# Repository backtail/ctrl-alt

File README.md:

# CTRL+ALT

CTRL+ALT is a modular firmware and hardware platform for a STM8 microcontroller, focused on real-time audio, control voltage (CV), and lo-fi digital signal processing. It is designed for experimentation, eurorack synths and embedded control projects.

Currently, the framework comes with these example projects to help you get started and familiarise yourself on how to access the functionalities:
- blinky
- master clock
- sample & hold
- wavetable LFO

If you fork this repo and come up with your own cool program, feel free to contribute so that everyone can enjoy it!

## Getting Started

### Prerequisites

- [PlatformIO](https://platformio.org/) (for building and uploading firmware)
- [ctrl+alt](https://www.maxgenson.de/ctrl-alt/) eurorack module
- STM8 debug probe
- [VSCode](https://code.visualstudio.com/) (optional, but really good integration and generally recommended for this project)
- [VSCodium](https://vscodium.com/) (optional, PlatformIO not natively supported, however workaround [exists](https://www.kentoseth.com/posts/2023/mar/22/install-platformio-ide-in-vscodium-flatpak/))

### Getting Started

Install VSCode with PlatformIO Plugin (recommended) or the PlatformIO CLI tool.

```sh
$ git clone https://github.com/backtail/ctrl-alt
$ cd ctrl-alt
$ code . # open VSCode
```

All example projects are located in `src/programs/`.

### Building

Use the VSCode/Codium PIO task and set the right project/environment. (recommended)

or

```sh
$ pio run -e <project_name>
```

### Upload

Use the VSCode/Codium PIO task and set the right project/environment. (recommended)

or

```sh
$ pio run -e <project_name> -t upload
```

## The Complementary Hardware

This framework is made to run on the 6 HP wide CTRL+ALT eurorack module which can be found under `hardware/`.

It features:
- 3 logic inputs (threshold ~ 2.5V, 12V tolerable) + indicator LEDs
- 3 CV inputs (0V to 5V, 12V tolerable)
- 3 knobs
- up to 3 CV outputs (0V to 5V) or up to 3 logic outputs (0V or 5V) + indicator LEDs -> per output switchable via software
- 1 toggle switch
- 1 momentary button switch

## Contributing

Please read [CONTRIBUTING.md]() for details on our code of conduct, and the process for submitting pull requests to us.

### Authors

* **[Max Genson](https://www.maxgenson.de/)** - Engineer @ [KOMA Elektronik](https://koma-elektronik.com/new/about-shop/)

## License
The underlying hardware project source code is licensed under [CERN Open Hardware Licence Version 2 - Strongly Reciprocal](LICENSE_HARDWARE). 

Everything else, including the source code of the firmware for the CTRL+ALT hardware is licensed under [GPL-3.0](LICENSE_SOFTWARE).

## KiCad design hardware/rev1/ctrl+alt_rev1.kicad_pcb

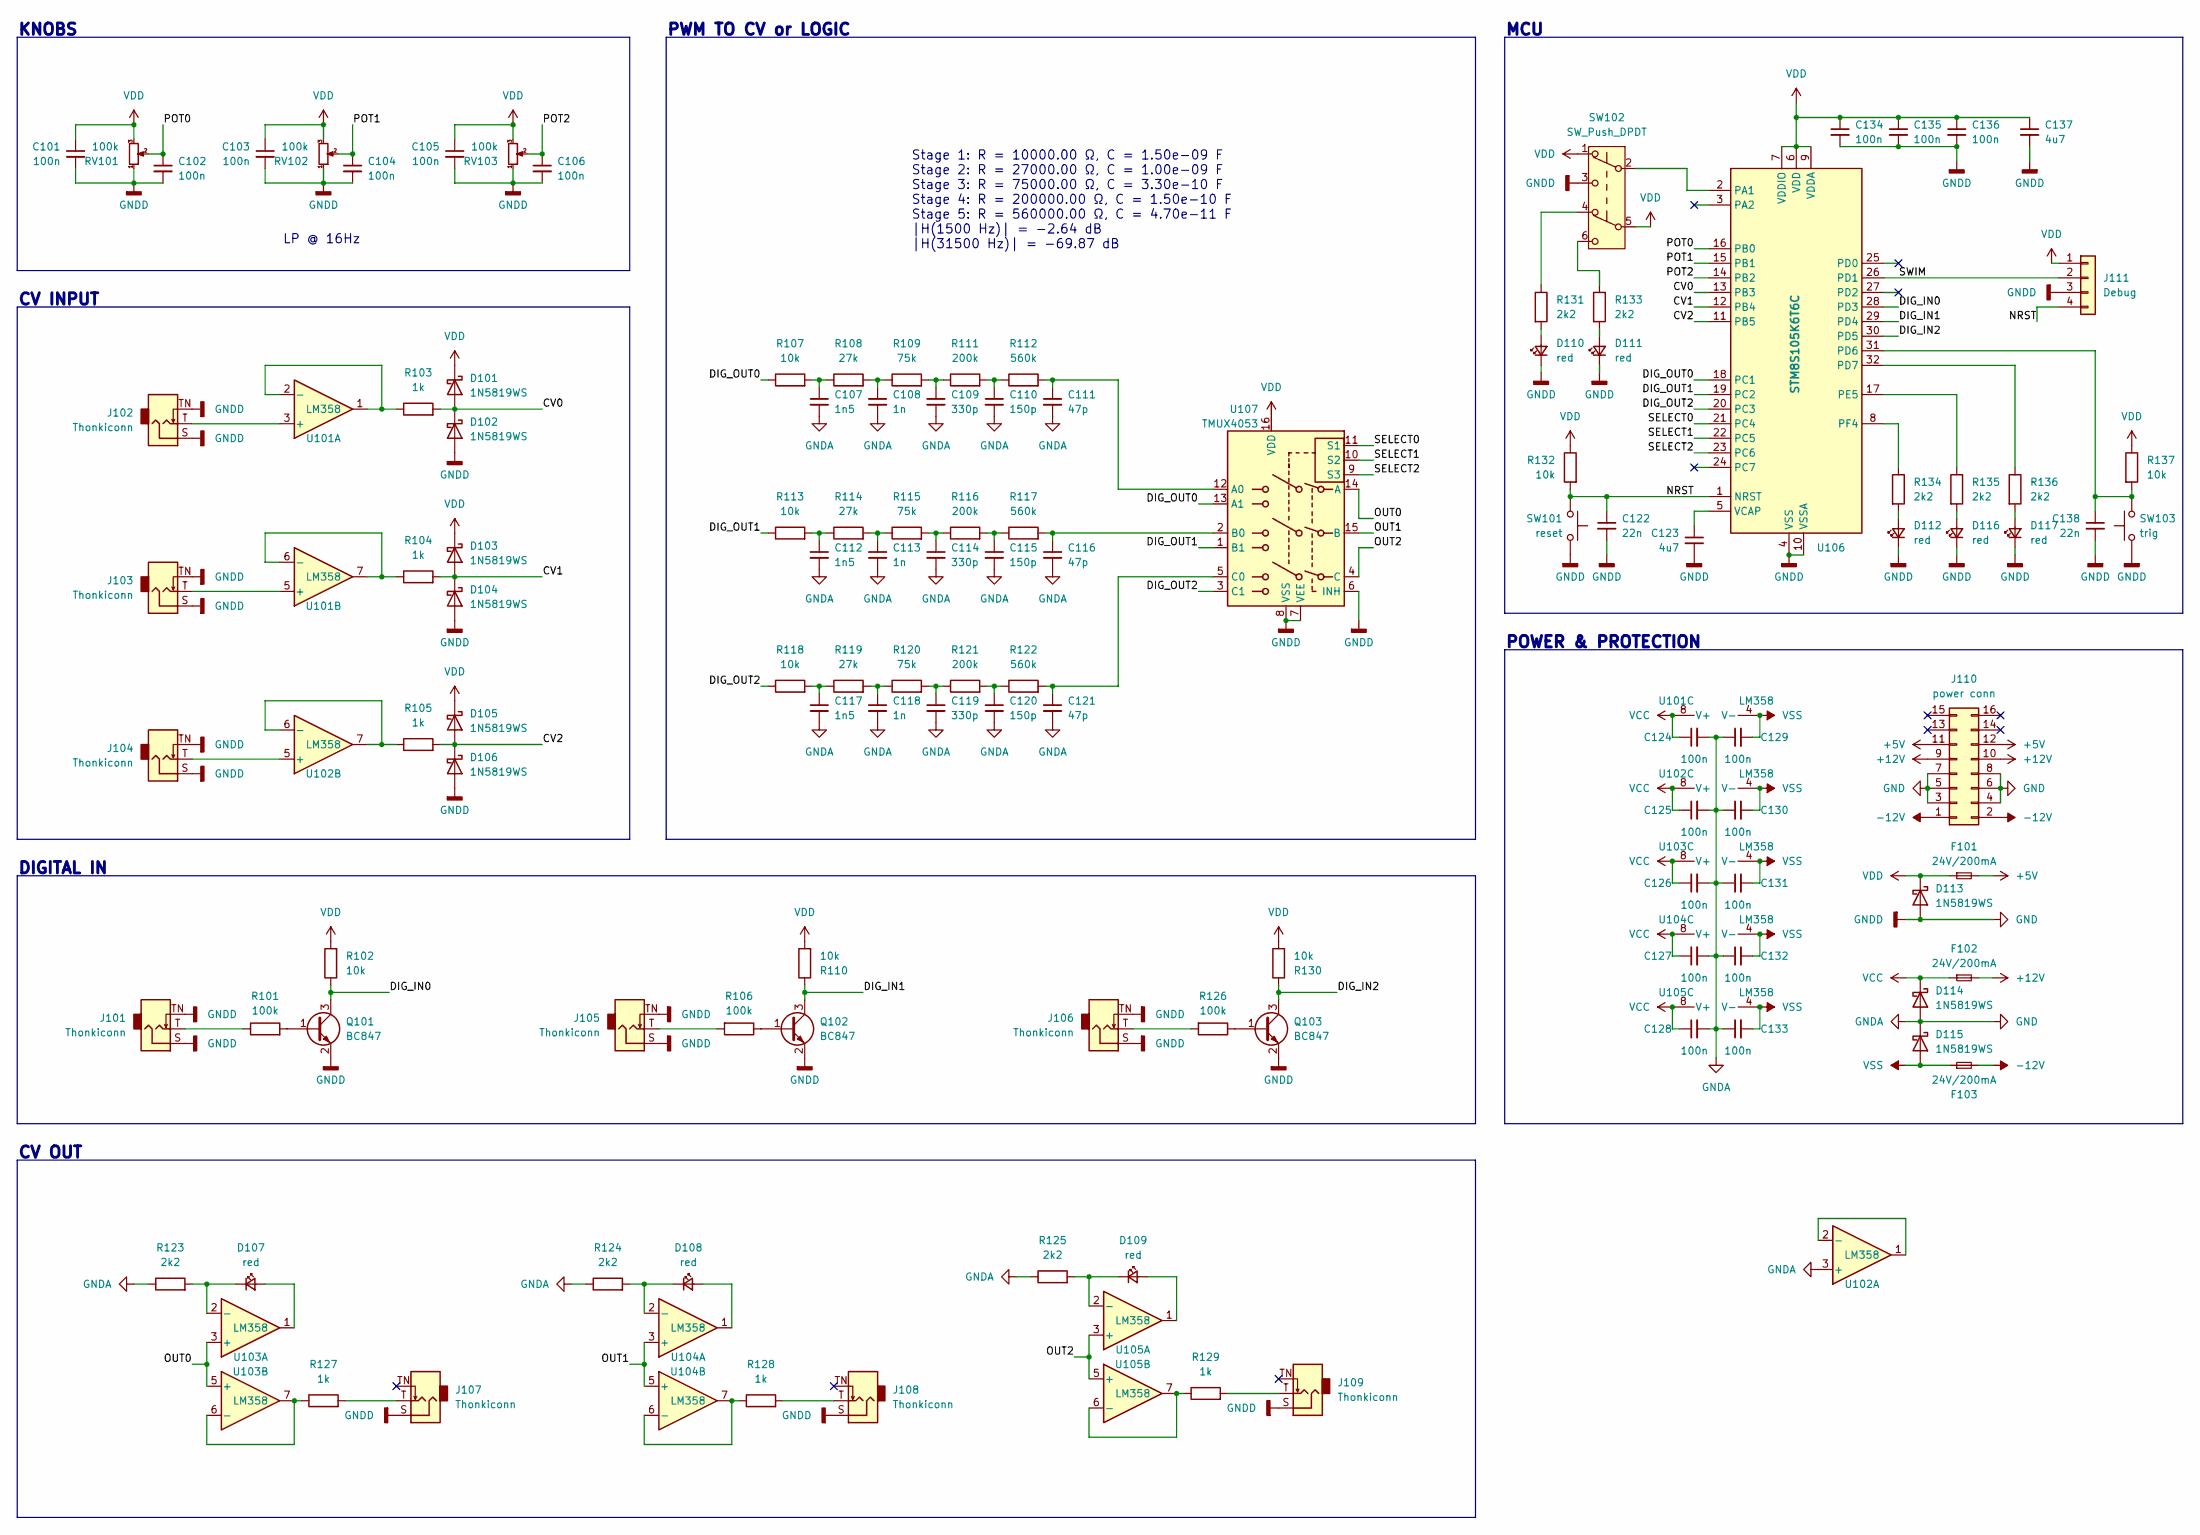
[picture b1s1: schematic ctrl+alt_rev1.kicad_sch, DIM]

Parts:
C101, C102, C103, C104, C105, C106, C124, C125, C126, C127, C128, C129, C130, C131, C132, C133, C134, C135, C136: 100n; C_0402_1005Metric; LCSC Part # C1523
C107, C112, C117: 1n5; C_0603_1608Metric; LCSC Part # C1595
C108, C113, C118: 1n; C_0402_1005Metric; LCSC Part # C1523
C109, C114, C119: 330p; C_0402_1005Metric; LCSC Part # C13533
C110, C115, C120: 150p; C_0402_1005Metric; LCSC Part # C1527
C111, C116, C121: 47p; C_0402_1005Metric; LCSC Part # C1567
C122, C138: 22n; C_0402_1005Metric; LCSC Part # C1532
C123, C137: 4u7; C_0805_2012Metric; LCSC Part # C1779
D101, D102, D103, D104, D105, D106, D113, D114, D115: 1N5819WS; D_SOD-323; LCSC Part # C191023
D107, D108, D109, D110, D111, D112, D116, D117: red; LED_D1.8mm
F101, F102, F103: 24V/200mA; R_0805_2012Metric; LCSC Part # C910821
J101, J102, J103, J104, J105, J106, J107, J108, J109: Thonkiconn; Jack_3.5mm_Thonkiconn
J110: power conn; PinHeader_2x08_P2.54mm_Vertical_SMD; LCSC Part # C3294466
J111: Debug; PinHeader_1x04_P2.54mm_Vertical
Q101, Q102, Q103: BC847; SOT-23; LCSC Part # C7420337
R101, R106, R126: 100k; R_0603_1608Metric; LCSC Part # C25803
R102, R107, R110, R113, R118, R130, R132, R137: 10k; R_0603_1608Metric; LCSC Part # C25804
R103, R104, R105, R127, R128, R129: 1k; R_0603_1608Metric; LCSC Part # C21190
R108, R114, R119: 27k; R_0402_1005Metric; LCSC Part # C25771
R109, R115, R120: 75k; R_0402_1005Metric; LCSC Part # C25798
R111, R116, R121: 200k; R_0402_1005Metric; LCSC Part # C25764
R112, R117, R122: 560k; R_0603_1608Metric; LCSC Part # C23203
R123, R124, R125, R131, R133, R134, R135, R136: 2k2; R_0603_1608Metric; LCSC Part # C23162
RV101, RV102, RV103: 100k; Potentiometer_RK09_RV09_Vertical
SW101: reset; SW_SPST_TL3342; LCSC Part # C318884
SW102: SW_Push_DPDT; SW_5.8x5.8mm
SW103: trig; SW_PBS-110_Normally-Open_Push_Button; LCSC Part # C318884
U101, U102, U103, U104, U105: LM358; SOIC-8_3.9x4.9mm_P1.27mm; LCSC Part # C7950
U106: STM8S105K6T6C; LQFP-32_7x7mm_P0.8mm; LCSC Part # C8254
U107: TMUX4053; TSSOP-16_4.4x5mm_P0.65mm; LCSC Part # C5377936

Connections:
+5V: F101.2, J110.11, J110.12
+12V: F102.2, J110.9, J110.10
-12V: F103.2, J110.1, J110.2
/CV0: D101.2 (A), D102.1 (K), R103.2, U106.13 (PB3)
/CV1: D103.2 (A), D104.1 (K), R104.2, U106.12 (PB4)
/CV2: D105.2 (A), D106.1 (K), R105.2, U106.11 (PB5)
/DIG_IN0: Q101.3 (C), R102.1, U106.28 (PD3)
/DIG_IN1: Q102.3 (C), R110.1, U106.29 (PD4)
/DIG_IN2: Q103.3 (C), R130.1, U106.30 (PD5)
/DIG_OUT0: R107.1, U106.18 (PC1), U107.13 (A1)
/DIG_OUT1: R113.1, U106.19 (PC2), U107.1 (B1)
/DIG_OUT2: R118.1, U106.20 (PC3), U107.3 (C1)
/NRST: C122.1, J111.4, R132.2, SW101.2, U106.1 (NRST)
/OUT0: U103.3 (+), U103.5 (+), U107.14 (A)
/OUT1: U104.3 (+), U104.5 (+), U107.15 (B)
/OUT2: U105.3 (+), U105.5 (+), U107.4 (C)
/POT0: C102.1, RV101.2, U106.16 (PB0)
/POT1: C104.1, RV102.2, U106.15 (PB1)
/POT2: C106.1, RV103.2, U106.14 (PB2)
/SELECT0: U106.21 (PC4), U107.11 (S1)
/SELECT1: U106.22 (PC5), U107.10 (S2)
/SELECT2: U106.23 (PC6), U107.9 (S3)
/SWIM: J111.2, U106.26 (PD1)
GND: C101.2, C102.2, C103.2, C104.2, C105.2, C106.2, C107.2, C108.2, C109.2, C110.2, C111.2, C112.2, C113.2, C114.2, C115.2, C116.2, C117.2, C118.2, C119.2, C120.2, C121.2, C122.2, C123.2, C124.2, C125.2, C126.2, C127.2, C128.2, C129.1, C130.1, C131.1, C132.1, C133.1, C134.2, C135.2, C136.2, C137.2, C138.2, D102.2 (A), D104.2 (A), D106.2 (A), D110.1 (K), D111.1 (K), D112.1 (K), D113.2 (A), D114.2 (A), D115.1 (K), D116.1 (K), D117.1 (K), J101.S, J101.TN, J102.S, J102.TN, J103.S, J103.TN, J104.S, J104.TN, J105.S, J105.TN, J106.S, J106.TN, J107.S, J108.S, J109.S, J110.3, J110.4, J110.5, J110.6, J110.7, J110.8, J111.3, Q101.2 (E), Q102.2 (E), Q103.2 (E), R123.1, R124.1, R125.1, RV101.1, RV102.1, RV103.1, SW101.1, SW102.3 (C), SW103.1, U102.3 (+), U106.4 (VSS), U106.10 (VSSA), U107.6 (INH), U107.7 (VEE), U107.8 (VSS)
unnamed: C107.1, R107.2, R108.1
unnamed: C108.1, R108.2, R109.1
unnamed: C109.1, R109.2, R111.1
unnamed: C110.1, R111.2, R112.1
unnamed: C112.1, R113.2, R114.1
unnamed: C113.1, R114.2, R115.1
unnamed: C114.1, R115.2, R116.1
unnamed: C115.1, R116.2, R117.1
unnamed: C117.1, R118.2, R119.1
unnamed: C118.1, R119.2, R120.1
unnamed: C119.1, R120.2, R121.1
unnamed: C120.1, R121.2, R122.1
unnamed: D107.2 (A), U103.1
unnamed: D107.1 (K), R123.2, U103.2 (-)
unnamed: D108.2 (A), U104.1
unnamed: D108.1 (K), R124.2, U104.2 (-)
unnamed: D109.2 (A), U105.1
unnamed: D109.1 (K), R125.2, U105.2 (-)
unnamed: D110.2 (A), R131.2
unnamed: D111.2 (A), R133.2
unnamed: D112.2 (A), R134.2
unnamed: D116.2 (A), R135.2
unnamed: D117.2 (A), R136.2
unnamed: J101.T, R101.1
unnamed: J105.T, R106.2
unnamed: J106.T, R126.2
unnamed: J107.T, R127.2
unnamed: J108.T, R128.2
unnamed: J109.T, R129.2
unnamed: Q101.1 (B), R101.2
unnamed: Q102.1 (B), R106.1
unnamed: Q103.1 (B), R126.1
unnamed: R131.1, SW102.4 (A)
unnamed: R133.1, SW102.6 (C)
unnamed: J102.T, U101.3 (+)
unnamed: R103.1, U101.1, U101.2 (-)
unnamed: J103.T, U101.5 (+)
unnamed: R104.1, U101.6 (-), U101.7
unnamed: U102.1, U102.2 (-)
unnamed: J104.T, U102.5 (+)
unnamed: R105.1, U102.6 (-), U102.7
unnamed: R127.1, U103.6 (-), U103.7
unnamed: R128.1, U104.6 (-), U104.7
unnamed: R129.1, U105.6 (-), U105.7
unnamed: SW102.2 (B), U106.2 (PA1)
unnamed: C138.1, R137.2, SW103.2, U106.31 (PD6)
unnamed: R136.1, U106.32 (PD7)
unnamed: R135.1, U106.17 (PE5)
unnamed: R134.1, U106.8 (PF4)
unnamed: C123.1, U106.5 (VCAP)
unnamed: C111.1, R112.2, U107.12 (A0)
unnamed: C116.1, R117.2, U107.2 (B0)
unnamed: C121.1, R122.2, U107.5 (C0)
VCC: C124.1, C125.1, C126.1, C127.1, C128.1, D114.1 (K), F102.1, U101.8 (V+), U102.8 (V+), U103.8 (V+), U104.8 (V+), U105.8 (V+)
VDD: C101.1, C103.1, C105.1, C134.1, C135.1, C136.1, C137.1, D101.1 (K), D103.1 (K), D105.1 (K), D113.1 (K), F101.1, J111.1, R102.2, R110.2, R130.2, R132.1, R137.1, RV101.3, RV102.3, RV103.3, SW102.1 (A), SW102.5 (B), U106.6 (VDD), U106.7 (VDDIO), U106.9 (VDDA), U107.16 (VDD)
VSS: C129.2, C130.2, C131.2, C132.2, C133.2, D115.2 (A), F103.1, U101.4 (V-), U102.4 (V-), U103.4 (V-), U104.4 (V-), U105.4 (V-)

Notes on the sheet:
Stage 1: R = 10000.00 Ω, C = 1.50e-09 F Stage 2: R = 27000.00 Ω, C = 1.00e-09 F Stage 3: R = 75000.00 Ω, C = 3.30e-10 F Stage 4: R = 200000.00 Ω, C = 1.50e-10 F Stage 5: R = 560000.00 Ω, C = 4.70e-11 F |H(1500 Hz)| = -2.64 dB |H(31500 Hz)| = -69.87 dB
PWM TO CV or LOGIC
CV OUT
LP @ 16Hz
POWER & PROTECTION
CV INPUT
MCU
KNOBS
DIGITAL IN

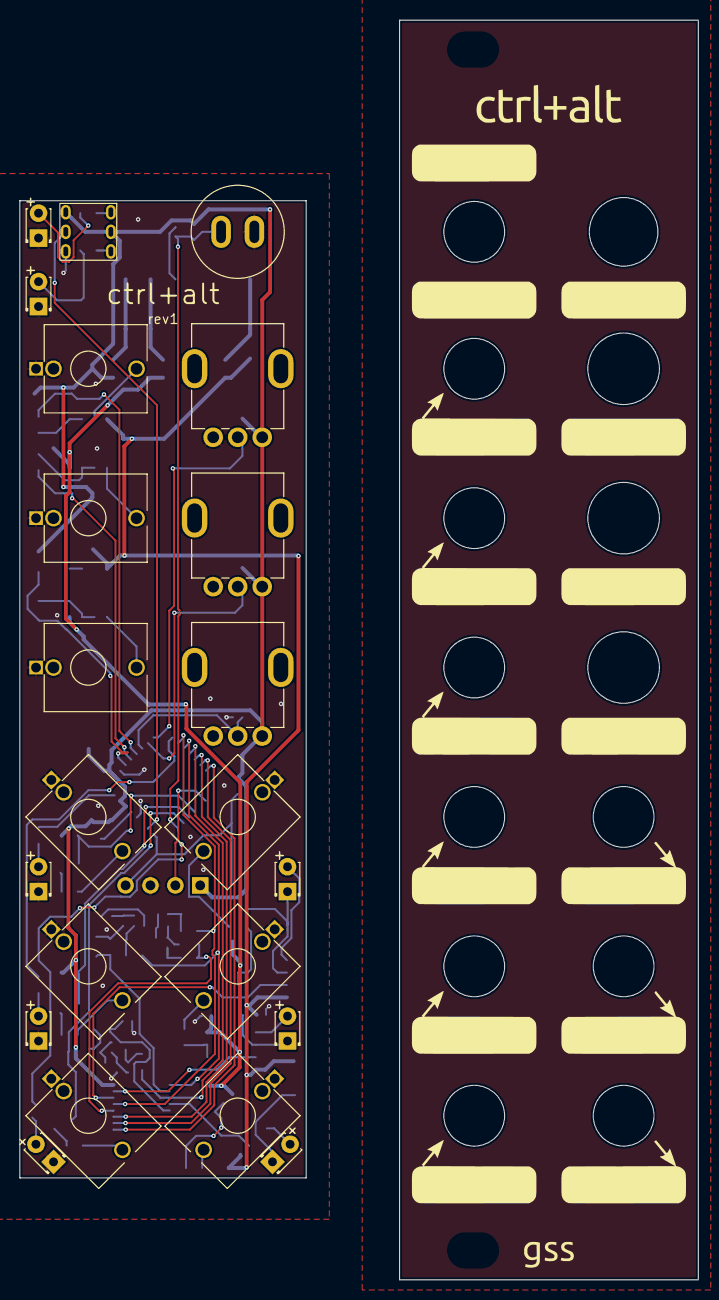
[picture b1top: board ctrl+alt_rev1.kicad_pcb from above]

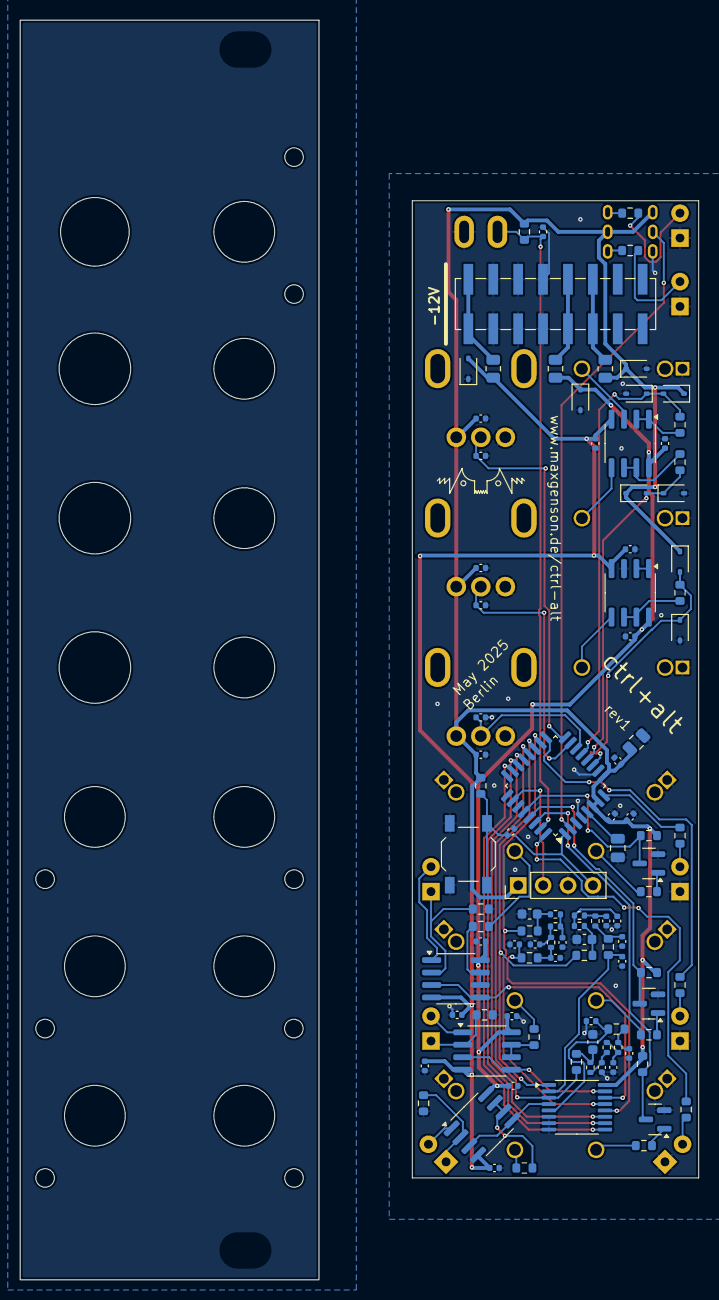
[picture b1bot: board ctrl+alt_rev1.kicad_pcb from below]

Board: 2 copper layers, 29.2 x 99.7 mm, 123 parts (101 on the bottom side), 80 nets.

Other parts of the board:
  : silkscreen_alien_small

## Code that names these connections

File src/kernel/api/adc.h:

#ifndef _K_API_ADC_
#define _K_API_ADC_

#include "stdint.h"

/// @brief ADC channel enumeration
typedef enum adc_channel
{
    POT0 = 0,
    POT1 = 1,
    POT2 = 2,
    CV0 = 3,
    CV1 = 4,
    CV2 = 5,
} adc_channel_t;

/// @brief ADC configuration structure
/// @param ch ADC channel to get the value from
/// @return ADC value from the specified channel (10-bit resolution)
uint16_t get_adc(adc_channel_t ch);

#endif //_K_API_ADC_

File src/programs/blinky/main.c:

#include "user_program.h"

#include "kernel/api/gpio.h"
#include "kernel/misc/delay.h"

uint8_t led_state = 1;

void set_all_pins(void)
{
    set_pin(&LED0, led_state & 0b001);
    set_pin(&LED1, led_state & 0b010);
    set_pin(&LED2, led_state & 0b100);

    set_pin(&OUT0, led_state & 0b001);
    set_pin(&OUT1, led_state & 0b010);
    set_pin(&OUT2, led_state & 0b100);
}

void setup() {}

void start() {}

void update()
{
    led_state <<= 1;
    if (led_state > (1 << 2))
        led_state = 1;

    set_all_pins();

    delay_us(500000);
}

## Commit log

2024-12-15 fix dac_lactency = 1
2024-12-15 add s&h program
2024-12-15 fix debugging
2024-12-15 make header guards unique
2024-12-15 setup master clock program
2024-12-15 add user start function
2024-12-15 add tim1 update interrupt handler access
2024-12-15 add master clokc and multiplier clock
2024-12-16 add first working implementation
2024-12-17 define adc sample rate for blinky example
2025-05-16 each program is now its own project target
2025-05-16 python based stm8s_conf.h header generation
2025-05-16 remove stm8s_conf.h
2025-05-16 add custom build scipts to projects
2025-05-16 remove unnecessary include
2025-05-17 add documention and generation with doxgen
2025-06-20 update gitignore
2025-06-20 add licenses
2025-06-20 add hardware
2025-06-20 update docs
2025-06-20 add docs deployment
2025-06-20 fix naming error
2025-06-20 Deploying to gh-pages from @ backtail/ctrl-alt@344bdeac9992888ef69f6f886ebb3addaceec841 🚀
2025-06-20 Initial gh-pages commit
2025-06-22 fix broken links
2025-06-22 Deploying to gh-pages from @ backtail/ctrl-alt@937fed5008e373d6811199802540ee47fdd0401c 🚀
